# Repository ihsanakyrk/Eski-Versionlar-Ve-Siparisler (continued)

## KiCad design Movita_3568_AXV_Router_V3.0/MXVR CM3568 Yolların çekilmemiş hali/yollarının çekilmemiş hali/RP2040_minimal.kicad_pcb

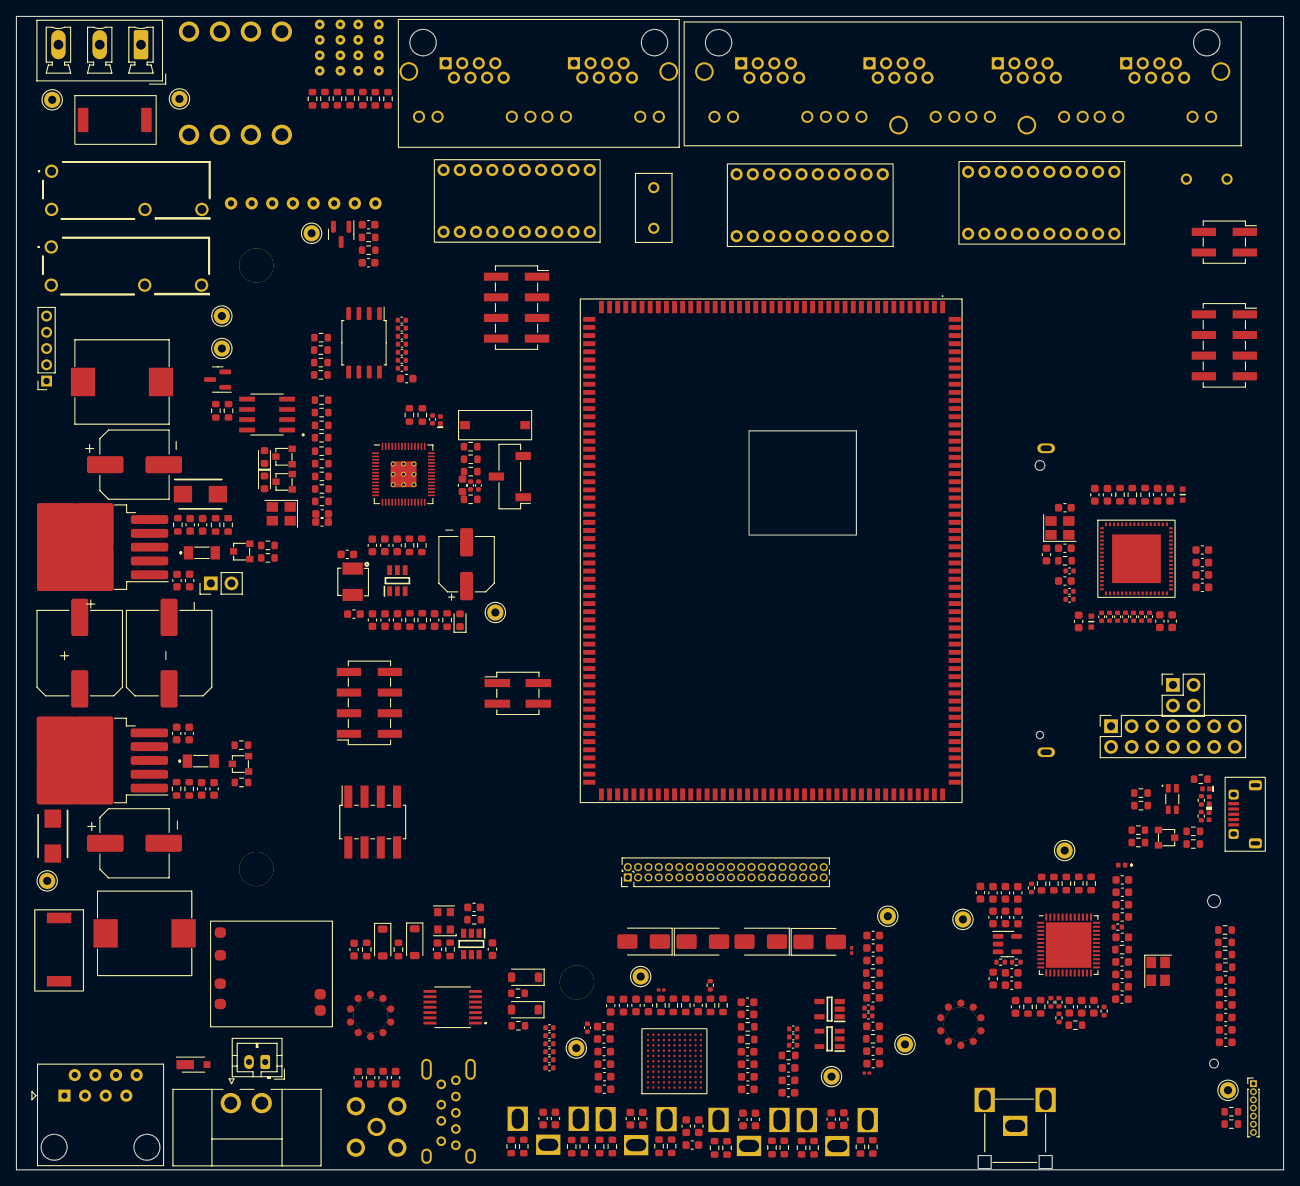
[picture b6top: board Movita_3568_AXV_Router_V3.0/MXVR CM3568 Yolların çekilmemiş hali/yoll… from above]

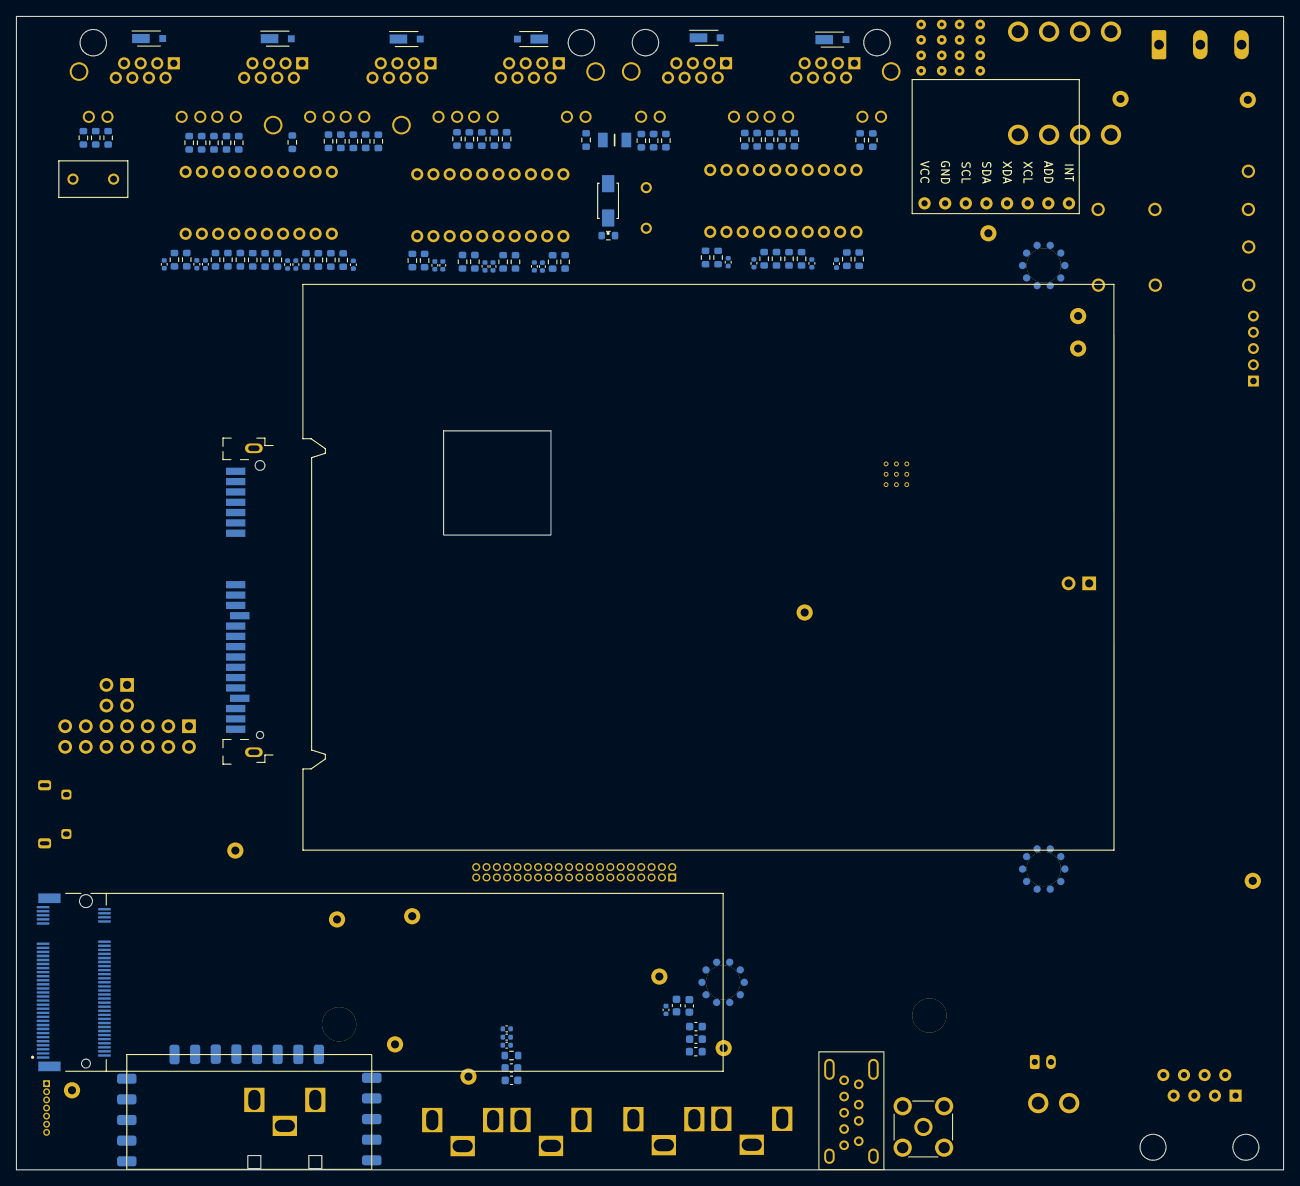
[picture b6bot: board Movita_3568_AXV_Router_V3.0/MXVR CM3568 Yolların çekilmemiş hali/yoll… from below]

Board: 4 copper layers, 156.0 x 142.0 mm, 480 parts (108 on the bottom side), 341 nets, no tracks yet.

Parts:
C1, C2, C3, C31, C40, C41, C42, C43, C44, C45, C46, C47, C48, C49, C50, C51, C52, C54, C55, C56, C57, C58, C59, C60, C101, C102, C103, C104, C105, C106, C107, C108, C109, C110, C116, C117, C118, C119, C120, C121, C124, C125, C126, C127, C143, C144, C147, C148, C150, C152, C156, C157, C158, C159, C160, C161, C162, C163, C165, C182, C183: 0.1uF; C_0603_1608Metric
C4, C6, C12: 4.7uF; C_0201_0603Metric
C7, C10, C37, C151, C155: 10uF; C_0603_1608Metric
C8, C9, C11, C13, C16, C17, C20, C21, C22, C23, C24, C25, C26, C27: 100nF; C_0402_1005Metric
C14, C15: 27pF; C_0603_1608Metric
C18, C19, C53, C128, C139, C140: 1uF; C_0603_1608Metric
C28, C83: 220uF/50V; C_Elec_10x10.2
C29, C30, C84, C169, C170, C172: 1uF/50V; C_0603_1608Metric
C32, C82: 330uF/25V; C_Elec_8x10.2
C35, C94, C166: 10pF; C_0603_1608Metric
C36, C38, C74, C75, C77, C95, C96, C97, C98, C99, C100, C111, C178: 100nF; C_0603_1608Metric
C39, C61: 33pF; C_0603_1608Metric
C62, C69, C180, C181: 22uF; C_0603_1608Metric
C63, C64, C65, C66, C67, C68, C70, C71, C72, C73, C76, C78, C79, C80, C81, C85, C86, C87, C88, C89, C90, C91: 0.1uF; C_0402_1005Metric
C92, C93: 1000PF 2KV; S102K33Y5PP63K5R
C112, C113, C129, C130, C131, C132, C133, C134, C135, C136, C137, C138, C141, C142: 10uF; C_0402_1005Metric
C114, C115: 4.7uF; C_0402_1005Metric
C122, C123: 8pF; C_0603_1608Metric
C145, C146, C179: 22pF; C_0603_1608Metric
C149, C154: 4.7uF; C_0603_1608Metric
C153: 10nF; C_0603_1608Metric
C164: DNP; C_0603_1608Metric
C171, C174: 0.33uF 16V; C_0603_1608Metric
C175, C176, C177: 10uF /16V; C_0603_1608Metric
C184: 220uF/16V; CP_Elec_6.3x7.7
D1, D2, D4, D5, D7, D8, D9: 2SS100L-W; 2SS100LW
D3: SS14; DIOM4325X250N
D6, D12, D13, D30: ESD5341N
D10, D11: SS54B; DIOM5336X244N
D14, D15, D16, D17: B5819W; D_SOD-123
D18, D19, D20, D21: SMAJ30CA; D_SMA
D22: ESD5451N
D23, D24: LL4148
D25: LED; LED_0603_1608Metric
D26, D27: MRA4007T3G; D_0603_1608Metric
D28, D29: S6MC
FB1: HI1206N101R-10; BEADC3216X130N
FL1: DLW31SN900SQ2L; DLW31SH222SQ2L
FL3, FL4: BLM18PG121SN1D; BLM18AG102BH1D
IC1: SN74LVC125APWR
IC2: MS1836S_QFN48-7x7; QFN-48-1EP_7x7mm_P0.5mm_EP5.6x5.6mm
IC3: RTL8309N
IC5: SY8113B; SOT95P285X100-6N
J1: FEMALE SMD Pin Header; PinSocket_2x07_P2.54mm_Vertical
J2, J18, J19, J20, J26: Phono RCA Jack Mono Connector Solder (Boktech adv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; AV_CON
J3: DNP; PinSocket_2x04_P2.54mm_Vertical_SMD
J4: DNP; PinSocket_1x05_P2.00mm_Vertical
J5: RJ45; RJ45_Amphenol_54602-x08_Horizontal
J6: MALE SMD Pin Header; PinHeader_2x20_P1.27mm_Vertical
J7: Conn_01x02_Socket; KF2EDGH-3.81-2P
J8: APCI0079-P002A J8900 M.2 M Key; TE_1-2199119-5
J9: Conn_01x06_Pin; RTL8188EU
J10: SMA Connetor_inner_hole; SMA_Connector_inner_pin_right_angle
J11: Conn_01x03_Socket; KF2EDGR-Y-5.08-3P-Right Angle
J12: Conn_01x08_Socket; KF2EDGH-3.81_8P
J13: FEMALE SMD Pin Header; PinSocket_2x04_P2.00mm_Vertical_SMD
J14: KH-MICRO5P-JN
J15, J16: Conn_01x08_Socket; LED_4_Block
J17: Conn_01x02_Socket; JST_PH_B2B-PH-K_1x02_P2.00mm_Vertical
J21, J22: FEMALE SMD Pin Header; PinSocket_2x04_P2.54mm_Vertical_SMD
J23, J28: M3x*0.5 L=10; Screw_terminal_shinbo
J24: USB 3.0 AF; CP-USB-3015
J25: DNP; PinHeader_2x02_P2.54mm_Vertical_SMD
J27: DNP; PinHeader_1x07_P1.00mm_Vertical
J29, J30: M3x*0.5 L=6; Screw_terminal_shinbo
J31: Conn_01x04_Socket; PinSocket_2x02_P2.54mm_Vertical
J32: DNP; PinHeader_1x02_P2.54mm_Vertical
J33: Conn_01x04_Socket; PinSocket_2x02_P2.54mm_Vertical_SMD
J34: FEMALE SMD Pin Header; PinSocket_1x03_P2.54mm_Vertical_SMD_Pin1Left
J35: M3x*0.5 L=3; Screw_terminal_shinbo
K1, K3: HF46F_5-HS1; HF46F5HS1
L2, L3: 47uH 5A; L_Bourns_SRR1208_12.7x12.7mm
L4, L5: FB/100R; L_0603_1608Metric
L6: UPZ1608E101-3R0TF; L_0603_1608Metric
L7: MLI1608F-1R2KT; L_0603_1608Metric
L8: HA42-4R7MT; Inductor_0402_4.7uH
L9: 2.7nH; L_0603_1608Metric
PS2: RT9013-33GB; SOT94P279X130-5N
PS3: TLV75712PDBVR; SOT95P280X145-5N
Q1: 2N3904S-RTK/PS; 2N3904S-RTKPS
Q2, Q3, Q4, Q5: MMBT2222ALT1G
R1: 150R; R_0603_1608Metric
R2, R3, R18, R19, R20, R35, R36, R40, R41, R43, R44, R47, R49, R55, R58, R59, R60, R61, R62, R63, R64, R65, R66, R67, R68, R69, R70, R71, R72, R78, R80, R82, R94, R95, R96, R97, R98, R99, R100, R101, R104, R107, R119, R122, R124, R136, R137, R155, R158, R159, R164, R169, R171: 10K; R_0603_1608Metric
R4, R5, R7, R9, R11, R25, R46, R54, R109, R113, R123, R126, R127: 0R; R_0603_1608Metric
R6, R8: 2.49K 1%; R_0603_1608Metric
R10, R12, R13, R21, R23, R24, R37, R38, R39, R42, R48, R77, R79, R81, R83, R84, R85, R86, R87, R88, R89, R90, R91, R92, R93, R105, R106, R132, R170, R172: 1K; R_0603_1608Metric
R14: 200R; R_0603_1608Metric
R15: 1R; R_0603_1608Metric
R16, R17: 27R; R_0603_1608Metric
R22, R26, R29, R50, R154, R163, R167, R173: DNP; R_0603_1608Metric
R27, R28, R32, R33, R34, R117, R118, R120: 4.7K; R_0603_1608Metric
R30, R31: 2.2R; R_0402_1005Metric
R45, R53, R108, R112, R116, R125, R146: 100R; R_0603_1608Metric
R51, R52, R56, R57, R73, R74, R75, R76, R102, R103, R110, R111, R114, R115: 75R; R_0603_1608Metric
R121, R129, R138: DNP; R_0402_1005Metric
R128: 560K; R_0603_1608Metric
R130: 10K %1; R_0402_1005Metric
R131, R133, R134, R139: 0R; R_0402_1005Metric
R135: 330R %1; R_0603_1608Metric
R140, R141: 2.2K; R_0603_1608Metric
R142: 22R; R_0603_1608Metric
R143: 75R; R_0402_1005Metric
R144: 100K; R_0603_1608Metric
R145: 1K %5; R_0603_1608Metric
R147, R148, R149, R150, R151, R152, R153: 220R; R_0603_1608Metric
R156: 3.3K 1%; R_0603_1608Metric
R157, R160: 470R; R_0603_1608Metric
R161: 15K; R_0603_1608Metric
R162: 1.6K; R_0603_1608Metric
R165: 232K_1%; R_0603_1608Metric
R166: 51K_1%; R_0603_1608Metric
R168: 2K; R_0603_1608Metric
S1: TS-1101-C-W
TP1, TP2, TP3, TP4, TP5, TP6, TP7, TP8, TP9, TP10, TP11, TP12, TP13, TP14, TP15: TestPoint; Pin_D1.0mm_L10.0mm
U1: CM3568
U2, U3: TLV76033DBZT; SOT-23
U4: 3N27000G33YC; Oscillator_SMD_EuroQuartz_XO32-4Pin_3.2x2.5mm
U5: RP2040; RP2040-QFN-56
U6: MAX485E; SOIC127P600X175-8N
U6B1: Nextchip N4; N4
U7: W25Q128JVS; SOIC-8_5.23x5.23mm_P1.27mm
U8: NL27WZU04DTT1G; SOP95P275X110-6N
U9: DNP; HDMI
U10, U15: XL4015; TO-263-5_TabPin3
U11: DNP; module_mpu6050
U12, U13, U19: UTH20T29 2220X; RJ45_Transformer_2_Port
U14: RT9013-12GB; SOT-23-5
U16: 5622-1200-ML; SATA_Connector_5622-1200-ML
U17: RJ45-4-Block; 4_Block_RJ45
U18: 2_Block_RJ45
Y1: 12000Mhz; Crystal_SMD_3225-4Pin_3.2x2.5mm
Y2: X322527MSB4SI; Crystal_SMD_3225-4Pin_3.2x2.5mm
Y4: 25MHz; Crystal_SMD_3225-4Pin_3.2x2.5mm

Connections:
1V0: C38.2, C74.2, C75.2, C95.2, C97.2, FL4.2, IC3.33 (DVDDL_2)
1V0PLL: C99.2, C100.2, FL4.1
3.3V_Sensor: C36.1, C41.1, D3.A, R27.1, R28.2, U2.1 (OUT), U11.1 (VCC)
3V3: C96.2, C98.2
+1V1: C16.1, C17.1, C18.1, U5.23 (DVDD), U5.45 (VREG_VOUT), U5.50 (DVDD)
/4 Port RJ45 and Transformer/+3.3V: C2.1, C4.1, C7.1, C55.1, C56.1, C57.1, C58.1, C59.1, C60.1, C114.1, C118.1, C179.2, C180.2, C181.2, C182.2, C183.2, C184.1, FB1.1, FL3.1, J6.5, J6.6, J8.2, J8.4, J8.12, J8.14, J8.16, J8.18, J8.70, J8.72, J8.74, J9.1, J21.1, L6.1, L8.2, PS3.1 (IN), R3.2, R154.1, R165.1, R168.1, TP3.1, TP9.1
/4 Port RJ45 and Transformer/LED0: IC3.38 (P0LED/DIS_EEE), R37.1, R38.2, R72.2
/4 Port RJ45 and Transformer/LED1: IC3.39 (P1LED/LED_MODE[1]), R23.1, R24.2, R78.2
/4 Port RJ45 and Transformer/LED2: IC3.40 (P2LED/LED_MODE[2]), R39.1, R42.2, R80.2
/4 Port RJ45 and Transformer/LED3: IC3.42 (P3LED/RMAMODE), R82.2, R84.1, R85.2
/4 Port RJ45 and Transformer/LED4: IC3.43 (P4LED/UNKOWN_MULTI), R86.1, R87.2, R104.2
/4 Port RJ45 and Transformer/LED5: IC3.44 (P5LED/DIS_RST_BLNK), R88.1, R89.2, R107.2
/4 Port RJ45 and Transformer/RXI_0_N: IC3.57 (RXIN0), R71.2, U13.9
/4 Port RJ45 and Transformer/RXI_0_P: IC3.56 (RXIP0), R70.2, U13.10
/4 Port RJ45 and Transformer/RXI_1_N: IC3.63 (RXIN1), R64.2, U13.2
/4 Port RJ45 and Transformer/RXI_1_P: IC3.64 (RXIP1), R65.2, U13.1
/4 Port RJ45 and Transformer/RXI_2_N: IC3.3 (RXIN2), R63.2, U12.9
/4 Port RJ45 and Transformer/RXI_2_P: IC3.2 (RXIP2), R62.2, U12.10
/4 Port RJ45 and Transformer/RXI_3_N: IC3.9 (RXIN3), R47.2, U12.2
/4 Port RJ45 and Transformer/RXI_3_P: IC3.10 (RXIP3), R55.2, U12.1
/4 Port RJ45 and Transformer/RXI_4_N: IC3.14 (RXIN4), R95.2, U19.9
/4 Port RJ45 and Transformer/RXI_4_P: IC3.13 (RXIP4), R94.2, U19.10
/4 Port RJ45 and Transformer/RXI_5_N: IC3.20 (RXIN5), R99.2, U19.2
/4 Port RJ45 and Transformer/RXI_5_P: IC3.21 (RXIP5), R98.2, U19.1
/4 Port RJ45 and Transformer/TXO_0_N: IC3.58 (TXON0), R69.2, U13.7
/4 Port RJ45 and Transformer/TXO_0_P: IC3.59 (TXOP0), R68.2, U13.6
/4 Port RJ45 and Transformer/TXO_1_N: IC3.62 (TXON1), R66.2, U13.4
/4 Port RJ45 and Transformer/TXO_1_P: IC3.61 (TXOP1), R67.2, U13.5
/4 Port RJ45 and Transformer/TXO_2_N: IC3.4 (TXON2), R61.2, U12.7
/4 Port RJ45 and Transformer/TXO_2_P: IC3.5 (TXOP2), R60.2, U12.6
/4 Port RJ45 and Transformer/TXO_3_N: IC3.8 (TXON3), R58.2, U12.4
/4 Port RJ45 and Transformer/TXO_3_P: IC3.7 (TXOP3), R59.2, U12.5
/4 Port RJ45 and Transformer/TXO_4_N: IC3.15 (TXON4), R96.2, U19.7
/4 Port RJ45 and Transformer/TXO_4_P: IC3.16 (TXOP4), R97.2, U19.6
/4 Port RJ45 and Transformer/TXO_5_N: IC3.19 (TXON5), R100.2, U19.4
/4 Port RJ45 and Transformer/TXO_5_P: IC3.18 (TXOP5), R101.2, U19.5
/+12V: C32.1, C172.2, C174.2, C175.2, C176.2, C177.2, D1.2, D2.2, D4.2, D5.2, D7.2, D8.2, D9.2, IC5.5 (IN), J12.4, L3.2, R11.2, R161.1, R163.1, TP2.1, U16.P13 (VCC12), U16.P14 (VCC12), U16.P15 (VCC12), U17.P1_L_Led+, U17.P2_L_Led+, U17.P3_L_Led+, U17.P4_L_Led+, U18.P1_L_Led+, U18.P2_L_Led+
/CM3568/+5V: C1.1, C3.1, C6.1, C10.1, C82.1, C84.2, C115.1, C119.1, C171.2, D26.1 (K), D27.1 (K), J16.5, J21.2, J21.4, J24.1 (VBUS), K1.2 (COIL_2), K3.2 (COIL_2), L2.2, PS2.1 (VIN), R25.2, R32.1, R155.1, TP1.1, TP8.1, U1.143, U1.144, U16.P7 (VCC5), U16.P8 (VCC5), U16.P9 (VCC5)
/CM3568/GPIO4_C5_d: J34.1, R167.2, U1.156
/CM3568/GPIO4_C6_d: J34.2, U1.157, U5.26 (RUN)
/CM3568/HDMITX_CEC_M0: R142.1, U1.162, U9.17
/CM3568/HDMITX_SCL: IC2.46 (RXDDC_SCL), R141.1, U1.164, U9.20
/CM3568/HDMITX_SDA: IC2.45 (RXDDC_SDA), R140.1, U1.163, U9.19
/CM3568/HDMI_TX0N: IC2.4 (HDMI_RX0N), U1.1, U9.8
/CM3568/HDMI_TX0P: IC2.5 (HDMI_RX0P), U1.2, U9.7
/CM3568/HDMI_TX1N: IC2.7 (HDMI_RX1N), U1.3, U9.6
/CM3568/HDMI_TX1P: IC2.8 (HDMI_RX1P), U1.4, U9.5
/CM3568/HDMI_TX2N: IC2.10 (HDMI_RX2N), U1.5, U9.3
/CM3568/HDMI_TX2P: IC2.11 (HDMI_RX2P), U1.6, U9.2
/CM3568/HDMI_TXCLKN_PORT: IC2.1 (HDMI_RXCN), U1.201, U9.11
/CM3568/HDMI_TXCLKP_PORT: IC2.2 (HDMI_RXCP), U1.202, U9.10
/CM3568/HDMI_TX_HPDIN: R144.1, R145.2, U1.7, U9.16
/CM3568/MIC1_INN: J27.5, U1.122
/CM3568/PCIE20_REFCLKN: J3.6, J8.53, U1.9
/CM3568/PCIE20_REFCLKP: J3.5, J8.55, U1.8
/CM3568/PCIE20_RXN: J3.3, J8.43, U1.11
/CM3568/PCIE20_RXP: J3.4, J8.41, U1.10
/CM3568/PCIE20_TXN: J3.2, J8.47, U1.13
/CM3568/PCIE20_TXP: J3.1, J8.49, U1.12
/CM3568/PDM_SDI2_M0_ADC/PCIE20_WAKEn_M2: J8.54, U1.91
/CM3568/PHY1_MDI0+: IC3.28 (TXOP7), J33.1, U1.102
/CM3568/PHY1_MDI0-: IC3.29 (TXON7), J33.2, U1.103
/CM3568/PHY1_MDI1+: IC3.31 (RXIP7), J33.3, U1.104
/CM3568/PHY1_MDI1-: IC3.30 (RXIN7), J33.4, U1.105
/CM3568/RESETn: J27.1, U1.145
/CM3568/RK809_PWRON: J27.6, R26.1, R29.1, TP15.1, U1.141
/CM3568/SARADC_VIN0_KEY/RECOVERY: R146.1, U1.65
/CM3568/SATA0_RXN: U1.20, U16.S5 (RX-)
/CM3568/SATA0_RXP: U1.21, U16.S6 (RX+)
/CM3568/SATA0_TXN: U1.18, U16.S3 (TX-)
/CM3568/SATA0_TXP: U1.19, U16.S2 (TX+)
/CM3568/UART0_RX/PWM1_M0: U1.72, U5.27 (GPIO16)
/CM3568/UART0_TX/GPIO0_C1: U1.71, U5.28 (GPIO17)
/CM3568/USB2_HOST2_DM: J13.7, J22.4, U1.96
/CM3568/USB2_HOST2_DP: J13.5, J22.3, U1.97
/CM3568/USB2_HOST3_DM: J9.2, J22.6, U1.98
/CM3568/USB2_HOST3_DP: J9.3, J22.5, U1.99
/CM3568/USB3_HOST1_DM: J22.2, J24.2 (D-), U1.23
/CM3568/USB3_HOST1_DP: J22.1, J24.3 (D+), U1.24
/CM3568/USB3_HOST1_SSRXN: J24.5 (SSRX-), U1.16
/CM3568/USB3_HOST1_SSRXP: J24.6 (SSRX+), U1.17
/CM3568/USB3_HOST1_SSTXN: J24.8 (SSTX-), U1.14
/CM3568/USB3_HOST1_SSTXP: J24.9 (SSTX+), U1.15
/CM3568/USB3_OTG0_DM: FL1.4, R30.1, U1.26
/CM3568/USB3_OTG0_DP: FL1.1, R31.1, U1.25
/CM3568/USB3_OTG0_ID: D13.1, J14.4 (ID), R34.2, U1.55
/CM3568/USB3_OTG0_VBUSDET: R32.2, R33.1, U1.54
/CM3568/VCC_1V8_OUTPUT: C12.1, C31.1, R119.1, R122.1, TP10.1, U1.146
/CM3568/VRTC: J27.7, R1.2, U1.124
/CSI_AHD/AHD_RESET: C109.1, R122.2, R123.1, U6B1.K10 (RESETN)
/CSI_AHD/AVIN: D18.2 (A2), D19.2 (A2), D20.2 (A2), D21.2 (A2), J18.1, J18.2, J19.1, J19.2, J20.1, J20.2, J26.1, J26.2, R46.1, R54.1, R109.1, R113.1
/CSI_AHD/COAX1: IC1.2 (1A), U6B1.C2 (MPP1)
/CSI_AHD/COAX2: IC1.5 (2A), U6B1.C3 (MPP2)
/CSI_AHD/COAX3: IC1.9 (3A), U6B1.C4 (MPP3)
/CSI_AHD/COAX4: IC1.12 (4A), U6B1.C5 (MPP4)
/CSI_AHD/GPIO2_C6: R119.2, U6B1.H8 (IRQ)
/CSI_AHD/GPIO4_C4_d: IC1.10 (3~OE), R43.1
/CSI_AHD/LCDC_D22/UART3_TX_M1: IC1.13 (4~OE), R44.1
/CSI_AHD/LCDC_D23/UART3_RX_M1: IC1.1 (1~OE), R35.1
/CSI_AHD/PDM_CLK1_M0_ADC/SPDIF_TX_M0: IC1.4 (2~OE), R36.1
/CSI_AHD/SYS_CLK: R45.1, U8.6 (OUT*Y1)
/CSI_AHD/VINN1: C102.2, U6B1.E2 (VINN1)
/CSI_AHD/VINN2: C104.2, U6B1.G2 (VINN2)
/CSI_AHD/VINN3: C106.2, U6B1.J2 (VINN3)
/CSI_AHD/VINN4: C108.2, U6B1.L2 (VINN4)
/CSI_AHD/VINP1: C101.2, U6B1.D1 (VINP1)
/CSI_AHD/VINP2: C103.2, U6B1.F1 (VINP2)
/CSI_AHD/VINP3: C105.2, U6B1.H1 (VINP3)
/CSI_AHD/VINP4: C107.2, U6B1.K1 (VINP4)
/CSI_AHD/VIN_N1: C102.1, R52.2
/CSI_AHD/VIN_N2: C104.1, R57.2
/CSI_AHD/VIN_N3: C106.1, R111.2
/CSI_AHD/VIN_N4: C108.1, R115.2
/CSI_AHD/VIN_P1: C101.1, D15.1 (K), R46.2, R51.2
/CSI_AHD/VIN_P2: C103.1, D14.1 (K), R54.2, R56.2
/CSI_AHD/VIN_P3: C105.1, D17.1 (K), R109.2, R110.2
/CSI_AHD/VIN_P4: C107.1, D16.1 (K), R113.2, R114.2
/EC25_Sim/GSM_STATUS: J13.3, J16.6
/HDMI_CVBS/CVideo_OUT: C164.2, C165.1, D22.1, J2.1, J2.2, J31.1, L7.2
/HDMI_CVBS/DAC_R: C163.1, C164.1, IC2.31 (AV_OUT), L7.1, R143.2
/HDMI_CVBS/HDMI_RX_HPD: IC2.43 (HDMIRX_HPD), R145.1
/HDMI_CVBS/P/N_SEL: R131.1, R137.2, R138.1
/HDMI_CVBS/RSTn: C153.1, IC2.15 (RSTn), R136.1, R142.2
/HDMI_CVBS/RX_DET: IC2.42 (DVDD33_1), IC2.44 (HDMIRX_DET), R132.2
/HDMI_CVBS/VDD10_EPHY: C155.1, C157.1, C158.1, C159.1, C160.1, C161.1, C162.1, IC2.3 (AVDD12), IC2.9 (AVDD12_1), IC2.20 (DVDD12), IC2.40 (DVDD12_1), TP11.1, U14.5 (OUT)
/HDMI_CVBS/XTAL1: C145.1, IC2.27 (XTOUT), Y2.1
/HDMI_CVBS/XTAL2: C146.1, IC2.26 (XTIN), Y2.3
/IO Connector/FLASH: J12.5, K3.4 (COM)
/IO Connector/HORN: J12.6, K1.4 (COM)
/MIC+: J12.1, J27.4, U1.123
/Power Unit/+3V3_Mini: C19.1, C20.1, C21.1, C22.1, C23.1, C24.1, C25.1, C26.1, C27.1, R14.1, R18.2, R19.2, R22.1, R40.2, R41.2, R157.1, R160.1, U3.1 (OUT), U5.1 (IOVDD), U5.10 (IOVDD), U5.22 (IOVDD), U5.33 (IOVDD), U5.42 (IOVDD), U5.44 (VREG_IN), U5.48 (USB_VDD), U5.49 (IOVDD), U6.8 (VCC), U7.8 (VCC)
/RP2040/GPIO0: R27.2, U5.2 (GPIO0), U11.4 (SDA)
/RP2040/GPIO1: R28.1, U5.3 (GPIO1), U11.3 (SCL)
/RP2040/GPIO6: R147.1, U5.8 (GPIO6)
/RP2040/GPIO7: R171.1, R172.1, U5.9 (GPIO7)
/RP2040/GPIO8: R169.1, R170.1, U5.11 (GPIO8)
/RP2040/GPIO9: R148.1, U5.12 (GPIO9)
/RP2040/GPIO10: R149.1, U5.13 (GPIO10)
/RP2040/GPIO11: R150.1, U5.14 (GPIO11)
/RP2040/GPIO12: R151.1, U5.15 (GPIO12)
/RP2040/GPIO13: R152.1, U5.16 (GPIO13)
/RP2040/GPIO14: R153.1, U5.17 (GPIO14)
/RP2040/GPIO15: R20.2, R50.1, U5.18 (GPIO15)
/RP2040/GPIO19: R167.1, U5.30 (GPIO19)
/RP2040/GPIO20: R164.2, U5.31 (GPIO20)
/RP2040/GPIO21: J13.6, U5.32 (GPIO21)
/RP2040/GPIO22: R158.1, U5.34 (GPIO22)
/RP2040/GPIO23: R159.1, R173.1, U5.35 (GPIO23)
/RP2040/GPIO27_ADC1: D30.1, R48.1, R49.2, U5.39 (GPIO27_ADC1)
/RP2040/QSPI_SCLK: U5.52 (QSPI_SCLK), U7.6 (CLK)
/RP2040/QSPI_SD0: U5.53 (QSPI_SD0), U7.5 (DI(IO0))
/RP2040/QSPI_SD1: U5.55 (QSPI_SD1), U7.2 (DO(IO1))
/RP2040/QSPI_SD2: U5.54 (QSPI_SD2), U7.3 (IO2)
/RP2040/QSPI_SD3: U5.51 (QSPI_SD3), U7.7 (IO3)
/RP2040/QSPI_SS: R21.1, R22.2, U5.56 (QSPI_SS), U7.1 (~CS)
/RP2040/XIN: C14.1, U5.20 (XIN), Y1.3
/RP2040/XOUT: R13.1, U5.21 (XOUT)
/RP2040/~USB_BOOT: J4.3, R21.2
/RTL8309E/LED6: IC3.45 (P6LED), R90.1, R91.2
/RTL8309E/LED7: IC3.46 (P7LED), R92.1, R93.2
/SPK+: J12.3, J27.3, U1.118
/SPK-: J12.2, J27.2, U1.119
ADC_VREF: R14.2, R15.1
AVDD12: C129.1, C131.1, C133.1, C135.1, C137.1, C141.1, L4.1, PS3.5 (OUT), R126.1, R127.1, TP14.1, U6B1.D3 (AVDD12_CH1), U6B1.F3 (AVDD12_CH2), U6B1.H3 (AVDD12_CH3), U6B1.K3 (AVDD12_CH4)
AVDD12PLL: C140.1, C144.1, R127.2, U6B1.H4 (AVDD12_PLL)
AVDD12_MIPI: C139.1, C143.1, R126.2, U6B1.J7 (AVDD12_MIPI)
AVDD33: C53.1, C110.1, C130.1, C132.1, C134.1, C136.1, C138.1, C142.1, IC1.14 (VCC), L5.2, PS2.5 (VOUT), TP13.1, U6B1.E3 (AVDD33.1), U6B1.G3 (AVDD33.2), U6B1.J3 (AVDD33.3), U6B1.L3 (AVDD33.4)
CMT1: R76.2, U13.13
CMT2: R75.2, U13.18
CMT3: R74.2, U12.13
CMT4: R73.2, U12.18
CMT5: R103.2, U19.13
CMT6: R102.2, U19.18
CT: C8.1, C9.1, C11.1, C13.1, C62.1, C63.1, C64.1, C65.1, C66.1, C67.1, C68.1, C69.1, C71.1, C72.1, C73.1, C76.2, FL3.2, IC3.41 (DVDDH), IC3.49 (V33IN), IC3.50 (AVDDHPLL), IC3.60 (AVDDH_4), R8.1, R10.2, R23.2, R37.2, R39.2, R84.2, R86.2, R88.2, R90.2, R92.2, U12.3, U12.8, U13.3, U13.8, U19.3, U19.8
DVDD33: R120.1, U6B1.D5 (DVDD33.1), U6B1.D7 (DVDD33.3), U6B1.E8 (DVDD33.5), U6B1.G7 (DVDD33.4), U6B1.H6 (DVDD33.2)
Earth: C1.2, C2.2, C3.2, C4.2, C6.2, C7.2, C8.2, C9.2, C10.2, C11.2, C12.2, C13.2, C14.2, C15.2, C16.2, C17.2, C18.2, C19.2, C20.2, C21.2, C22.2, C23.2, C24.2, C25.2, C26.2, C27.2, C28.2, C29.1, C31.2, C32.2, C36.2, C37.2, C39.2, C40.1, C41.2, C42.1, C43.1, C44.1, C45.1, C46.1, C47.1, C48.1, C53.2, C54.2, C55.2, C56.2, C57.2, C58.2, C59.2, C60.2, C61.2, C62.2, C63.2, C64.2, C65.2, C66.2, C67.2, C68.2, C69.2, C70.2, C71.2, C72.2, C73.2, C77.2, C78.2, C79.2, C80.2, C81.2, C82.2, C83.2, C84.1, C85.2, C86.2, C87.2, C88.2, C89.2, C90.2, C91.2, C92.1, C94.2, C109.2, C110.2, C111.2, C112.2, C113.2, C114.2, C115.2, C116.2, C117.2, C118.2, C119.2, C120.2, C121.2, C122.1, C123.1, C124.2, C125.2, C126.2, C127.2, C128.2, C129.2, C130.2, C131.2, C132.2, C133.2, C134.2, C135.2, C136.2, C137.2, C138.2, C139.2, C140.2, C141.2, C142.2, C143.2, C144.2, C145.2, C146.2, C147.2, C148.2, C149.2, C150.2, C151.2, C152.2, C153.2, C154.2, C155.2, C156.2, C157.2, C158.2, C159.2, C160.2, C161.2, C162.2, C163.2, C165.2, C166.2, C169.1, C172.1, C175.1, C176.1, C177.1, C180.1, C181.1, C182.1, C183.1, C184.2, D6.2, D10.2, D11.2, D12.2, D13.2, D18.1 (A1), D19.1 (A1), D20.1 (A1), D21.1 (A1), D22.2, D25.1 (K), D30.2, IC1.7 (GND), IC2.19 (VSS), IC2.22 (VREF_L), IC2.30 (VSS_1), IC2.41 (VSS_2), IC2.49 (GND(EPAD)), IC3.65 (EP), IC5.2 (GND), J2.3, J4.4, J5.7, J5.8, J6.3, J6.4, J6.7, J6.8, J6.15, J6.16, J6.19, J6.20, J6.31, J6.32, J7.1, J8.1, J8.3, J8.9, J8.15, J8.21, J8.27, J8.33, J8.39, J8.45, J8.51, J8.57, J8.71, J8.73, J8.75, J8.SH1 (SHIELD), J8.SH2 (SHIELD), J9.4, J9.5, J10.2, J10.3, J10.4, J10.5, J11.2, J13.1, J13.2, J14.5 (GND), J14.SHIELD, J15.1, J15.3, J15.5, J15.7, J16.1, J16.3, J16.7, J17.1, J21.5, J21.6, J24.4 (GND), J24.7 (DRAIN), J24.10 (SHIELD), J31.2, J32.2, J34.3, PS2.2 (GND), PS3.2 (GND), Q1.2 (E), Q2.2 (E), Q3.2 (E), Q4.2 (E), Q5.2 (E), R6.2, R12.1, R24.1, R26.2, R33.2, R35.2, R36.2, R38.1, R42.1, R43.2, R44.2, R48.2, R50.2, R53.2, R77.2, R79.2, R81.2, R83.2, R85.1, R87.1, R89.1, R91.1, R93.1, R105.2, R106.2, R108.2, R112.1, R116.2, R117.2, R118.2, R121.2, R129.1, R130.1, R133.1, R135.1, R138.2, R143.1, R144.2, R156.2, R162.2, R166.2, R169.2, R171.2, S1.2, U1.22, U1.38, U1.62, U1.66, U1.95, U1.110, U1.140, U1.161, U1.190, U2.3 (GND), U3.3 (GND), U4.2 (GND2), U4.4 (GND1), U5.19 (TESTEN), U5.57 (GND), U6.5 (GND), U6B1.A1 (N.C1), U6B1.A11 (N.C2), U6B1.E5 (VSS3), U6B1.E6 (VSS6), U6B1.E7 (VSS8), U6B1.F4 (VSS1), U6B1.F5 (VSS4), U6B1.F6 (VSS7), U6B1.F7 (VSS9), U6B1.G4 (VSS2), U6B1.G5 (VSS5), U6B1.J4 (TEST1), U6B1.J8 (AVSS_MIPI), U6B1.K4 (TEST0), U6B1.K11 (TEST_CLK1), U6B1.L1 (N.C3), U6B1.L10 (TEST_CLK2), U6B1.L11 (N.C4), U7.4 (GND), U8.2 (GND), U9.4, U9.9, U9.12, U9.18, U10.1 (GND), U11.2 (GND), U14.2 (GND), U15.1 (GND), U16.GND, U16.P4 (GND), U16.P5 (GND), U16.P6 (GND), U16.P10 (GND), U16.P11 (GND), U16.P12 (GND), U16.S1 (GND), U16.S4 (GND), U16.S7 (GND), U17.7_1, U17.7_2, U17.7_3, U17.7_4, U17.8_1, U17.8_2, U17.8_3, U17.8_4, U18.7_1, U18.7_2, U18.8_1, U18.8_2, U18.SHIELD, Y1.2, Y1.4, Y2.2, Y2.4, Y4.2, Y4.4
GNDPWR: C92.2, C93.2, U17.SHIELD
LED_VDD: FB1.2, U17.P1_R_Led+, U17.P2_R_Led+, U17.P3_R_Led+, U17.P4_R_Led+, U18.P1_R_Led+, U18.P2_R_Led+
LIND_DS_LED: IC3.37 (LDIND/DIS_LD), R10.1, R12.2
unnamed: C15.1, R13.2, Y1.1
unnamed: C35.1, C94.1, L9.1
unnamed: C70.1, R47.1, R55.1
unnamed: C78.1, R94.1, R95.1
unnamed: C79.1, R96.1, R97.1
unnamed: C80.1, R98.1, R99.1
unnamed: C81.1, R100.1, R101.1
unnamed: C85.1, R58.1, R59.1
unnamed: C86.1, R60.1, R61.1
unnamed: C87.1, R62.1, R63.1
unnamed: C88.1, R64.1, R65.1
unnamed: C89.1, R66.1, R67.1
unnamed: C90.1, R68.1, R69.1
unnamed: C91.1, R70.1, R71.1
unnamed: C93.1, R73.1, R74.1, R75.1, R76.1, R102.1, R103.1
unnamed: C113.1, C117.1, C121.1, C125.1, C127.1, L5.1
unnamed: D3.C, R1.1
unnamed: D14.2 (A), IC1.6 (2Y)
unnamed: D15.2 (A), IC1.3 (1Y)
unnamed: D16.2 (A), IC1.11 (4Y)
unnamed: D17.2 (A), IC1.8 (3Y)
unnamed: D25.2 (A), R168.2
unnamed: D26.2 (A), K1.1 (COIL_1), Q4.3 (C)
unnamed: D27.2 (A), K3.1 (COIL_1), Q5.3 (C)
unnamed: IC2.29 (DAC_REF), R135.2
unnamed: IC2.16 (KEY0), R131.2
unnamed: IC2.17 (KEY1), R133.2
unnamed: IC2.12 (MCU_SEL), R129.2
unnamed: IC2.48 (REXT), R130.2
unnamed: C151.1, C152.1, IC2.25 (VMID)
unnamed: C149.1, C150.1, IC2.23 (VREF_H), R134.1
unnamed: C76.1, IC3.6 (AVDDH_1)
unnamed: C98.1, IC3.17 (AVDDH_2)
unnamed: C96.1, IC3.27 (AVDDH_3)
unnamed: C99.1, IC3.53 (AVDDLPLL)
unnamed: C74.1, IC3.1 (AVDDL_1)
unnamed: C75.1, IC3.11 (DVDDL_1), IC3.12 (AVDDL_2)
unnamed: C95.1, IC3.22 (AVDDL_3)
unnamed: C97.1, IC3.32 (AVDDL_4)
unnamed: C100.1, IC3.55 (AVDDL_5)
unnamed: C77.1, IC3.47 (DVDDL_3)
unnamed: IC3.54 (IBREF), R6.1
unnamed: C37.1, IC3.36 (RESETB), R8.2
unnamed: C38.1, IC3.48 (V10OUT)
unnamed: C178.1, IC5.1 (BS)
unnamed: IC5.4 (EN), R163.2, R164.1
unnamed: C179.1, IC5.3 (FB), R165.2, R166.1
unnamed: C178.2, IC5.6 (LX), L8.1
unnamed: J6.1, J6.2, R11.1, R25.1
unnamed: J6.9, R4.2
unnamed: J6.10, R7.1
unnamed: J6.11, R5.2
unnamed: J6.12, R9.1
unnamed: J6.13, Q1.3 (C), R3.1
unnamed: C35.2, J9.6
unnamed: C166.1, J10.1, L9.2
unnamed: D6.1, FL1.2, J14.3 (D+), R31.2
unnamed: D12.1, FL1.3, J14.2 (D-), R30.2
unnamed: J15.2, R147.2
unnamed: J15.4, R148.2
unnamed: J15.6, R149.2
unnamed: J15.8, R150.2
unnamed: J16.2, R151.2
unnamed: J16.4, R152.2
unnamed: J16.8, R153.2
unnamed: D4.1, D28.2, J7.2, J17.2
unnamed: J18.3, R51.1, R52.1, R53.1
unnamed: J19.3, R110.1, R111.1, R112.2
unnamed: J20.3, R114.1, R115.1, R116.1
unnamed: J26.3, R56.1, R57.1, R108.1
unnamed: D24.2, J32.1, Q2.3 (C), R160.2, R173.2
unnamed: C111.1, PS2.3 (EN), PS3.3 (EN), R124.2
unnamed: Q1.1 (B), R2.2
unnamed: Q2.1 (B), R159.2
unnamed: Q3.1 (B), R158.2
unnamed: D23.2, Q3.3 (C), R157.2
unnamed: Q4.1 (B), R170.2
unnamed: Q5.1 (B), R172.2
unnamed: R72.1, U17.P1_R_Led-
unnamed: R77.1, U17.P1_L_Led-
unnamed: R78.1, U17.P2_R_Led-
unnamed: R79.1, U17.P2_L_Led-
unnamed: R80.1, U17.P3_R_Led-
unnamed: R81.1, U17.P3_L_Led-
unnamed: R82.1, U17.P4_R_Led-
unnamed: R83.1, U17.P4_L_Led-
unnamed: R104.1, U18.P1_R_Led-
unnamed: R105.1, U18.P1_L_Led-
unnamed: R106.1, U18.P2_L_Led-
unnamed: R107.1, U18.P2_R_Led-
unnamed: R146.2, S1.1
unnamed: R154.2, U1.142
unnamed: C122.2, R125.1, U4.1 (XIN)
unnamed: C123.2, R128.2, U4.3 (XOUT), U8.3 (INA2)
unnamed: R15.2, U5.43 (ADC_AVDD)
unnamed: R17.2, U5.46 (USB_DM)
unnamed: R16.2, U5.47 (USB_DP)
unnamed: R20.1, U6.2 (~RE), U6.3 (DE)
unnamed: C54.1, U6B1.J6 (MIPI_VREFG)
unnamed: C44.2, C51.2, U6B1.D2 (REFB1)
unnamed: C45.2, C52.2, U6B1.F2 (REFB2)
unnamed: C42.2, C50.2, U6B1.H2 (REFB3)
unnamed: C40.2, C49.2, U6B1.K2 (REFB4)
unnamed: C47.2, C51.1, U6B1.C1 (REFT1)
unnamed: C48.2, C52.1, U6B1.E1 (REFT2)
unnamed: C46.2, C50.1, U6B1.G1 (REFT3)
unnamed: C43.2, C49.1, U6B1.J1 (REFT4)
unnamed: R118.1, U6B1.H7 (SA0)
unnamed: R117.1, U6B1.J5 (SA1)
unnamed: R120.2, R121.1, U6B1.J9 (SEL_18)
unnamed: R45.2, U6B1.L4 (SYS_CLK)
unnamed: R125.2, R128.1, U8.1 (INA1), U8.4 (OUT*Y2)
unnamed: C128.1, U8.5 (VCC)
unnamed: C30.1, U10.2 (FB)
unnamed: C174.1, D24.1, R161.2, R162.1, U10.4 (VC)
unnamed: D11.1, L3.1, U10.5 (VIN)
unnamed: R139.2, U14.3 (EN)
unnamed: C171.1, D23.1, R155.2, R156.1, U15.2 (FB)
unnamed: D10.1, L2.1, U15.3 (SW)
unnamed: C170.1, U15.4 (VC)
unnamed: D2.1, U17.4_1, U17.5_1
unnamed: D5.1, U17.4_2, U17.5_2
unnamed: D7.1, U17.4_3, U17.5_3
unnamed: D8.1, U17.4_4, U17.5_4
unnamed: D1.1, U18.4_1, U18.5_1
unnamed: D9.1, U18.4_2, U18.5_2
PCIE_CLK_NREQ: J3.7, J8.52, U1.92
PCIE_NRST: J3.8, J8.50, U1.90
RS485_A: J5.3, R40.1, U6.6 (A)
RS485_B: J5.2, R41.1, U6.7 (B)
RX: R19.1, U5.7 (GPIO5), U6.1 (RO)
RX0_N: U13.12, U17.2_1
RX0_P: U13.11, U17.1_1
RX1_N: U13.19, U17.2_2
RX1_P: U13.20, U17.1_2
RX2_N: U12.12, U17.2_3
RX2_P: U12.11, U17.1_3
RX3_N: U12.19, U17.2_4
RX3_P: U12.20, U17.1_4
RX4_N: U18.2_1, U19.12
RX4_P: U18.1_1, U19.11
RX5_N: U18.2_2, U19.19
RX5_P: U18.1_2, U19.20
TX: R18.1, U5.6 (GPIO4), U6.4 (DI)
TX0_N: U13.14, U17.6_1
TX0_P: U13.15, U17.3_1
TX1_N: U13.17, U17.6_2
TX1_P: U13.16, U17.3_2
TX2_N: U12.14, U17.6_3
TX2_P: U12.15, U17.3_3
TX3_N: U12.17, U17.6_4
TX3_P: U12.16, U17.3_4
TX4_N: U18.6_1, U19.14
TX4_P: U18.3_1, U19.15
TX5_N: U18.6_2, U19.17
TX5_P: U18.3_2, U19.16
VCC_3V3_S0: C147.1, C148.1, C154.1, C156.1, IC2.6 (AVDD33), IC2.18 (DVDD33), IC2.28 (AVDD33_1), IC2.34 (AVDD33_2), IC2.47 (AVDD33_3), L6.2, R132.1, R134.2, R136.2, R137.1, R139.1, R140.2, R141.2, TP12.1, U14.1 (IN)
VDD12: C112.1, C116.1, C120.1, C124.1, C126.1, L4.2, U6B1.D6 (DVDD12.2), U6B1.D8 (DVDD12.4), U6B1.F8 (DVDD12.5), U6B1.G6 (DVDD12.3), U6B1.H5 (DVDD12.1)
VIN: C28.1, C29.2, C30.2, C83.1, C169.2, C170.2, D28.1, D29.1, J4.5, J5.4, J5.5, J13.4, J13.8, K1.3 (NO), K3.3 (NO), R49.1, TP4.1, TP6.1, TP7.1, U2.2 (IN), U3.2 (IN), U10.3 (SW), U15.5 (VIN)
VRAW: D29.2, J11.1, TP5.1
XI: C39.1, IC3.52 (XI), Y4.1
XO: C61.1, IC3.51 (XO), Y4.3

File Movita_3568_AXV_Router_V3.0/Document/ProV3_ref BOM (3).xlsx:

Id | Designator | Footprint | Quantity | Designation | 1010pcs
1 | R15 | R_0603_1608Metric | 1 | 1R
2 | C17,C16,C24,C20,C26,C22,C27,C21,C23,C25,C8,C11,C9,C13 | C_0402_1005Metric | 14 | 100nF
3 | R130 | R_0402_1005Metric | 1 | 10K %1
4 | R169,R171,R158,R2,R3,R36,R18,R40,R19,R35,R20,R43,R119,R44,R164,R41,R124,R159,R1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 | R_0603_1608Metric | 53 | 10K
5 | R109,R5,R4,R113,R123,R25,R9,R126,R7,R54,R46,R127,R11 | R_0603_1608Metric | 13 | 0R
6 | C138,C137,C134,C141,C142,C136,C132,C130,C133,C135,C112,C129,C113,C131 | C_0402_1005Metric | 14 | 10uF
7 | U19,U13,U12 | RJ45_Transformer_2_Port | 3 | TF-218DG
8 | C4,C12,C6,C154,C149 | C_0603_1608Metric | 5 | 4.7uF
9 | R133,R139,R131,R134 | R_0402_1005Metric | 4 | 0R
10 | C92,C93 | S102K33Y5PP63K5R | 2 | 1000PF 2KV
11 | C171,C174 | C_0603_1608Metric | 2 | 0.33uF 16V
12 | D23,D24 | LL4148 | 2 | LL4148
13 | IC2 | QFN-48-1EP_7x7mm_P0.5mm_EP5.6x5.6mm | 1 | MS1836S_QFN48-7x7
14 | C84,C170,C30,C172,C169,C29 | C_0603_1608Metric | 6 | 1uF/50V
15 | D28,D29 | S6MC | 2 | S6MC
16 | FL4,FL3 | BLM18AG102BH1D | 2 | BLM18PG121SN1D
17 | D15,D14,D17,D16 | D_SOD-123 | 4 | B5819W
18 | R116,R53,R125,R45,R112,R108, R146 | R_0603_1608Metric | 6 | 100R
19 | R30,R31 | R_0402_1005Metric | 2 | 2.2R
20 | U1 | CM3568 | 1 | ~ | Fatih supply this part
21 | R57,R115,R52,R110,R111,R114,R51,R102,R75,R73,R103,R76,R74,R56 | R_0603_1608Metric | 14 | 75R
22 | R150,R148,R152,R149,R153,R147,R151 | R_0603_1608Metric | 7 | 220R
23 | C48,C47,C43,C44,C46,C116,C109,C56,C49,C182,C183,C51,C103,C58,C42,C104,C126,C60,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 | C_0603_1608Metric | 61 | 0.1uF
24 | C18,C128,C19,C53,C139,C140 | C_0603_1608Metric | 6 | 1uF
25 | PS3 | SOT95P280X145-5N | 1 | TLV75712PDBVR
27 | J16,J15 | LED_4_Block | 2 | Conn_01x08_Socket
28 | D11,D10 | DIOM5336X244N | 2 | SS54B
29 | C39,C61 | C_0603_1608Metric | 2 | 33pF
30 | R21,R48,R13,R12,R10,R24,R89,R90,R83,R93,R84,R23,R92,R85,R91,R81,R106,R77,R42,R3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 | R_0603_1608Metric | 30 | 1K
31 | J13 | PinSocket_2x04_P2.00mm_Vertical_SMD | 1 | FEMALE SMD Pin Header
33 | D19,D20,D21,D18 | D_SMA | 4 | SMAJ30CA
34 | TP5,TP15,TP13,TP4,TP1,TP14,TP7,TP3,TP2,TP9,TP11,TP12,TP8,TP10,TP6 | Pin_D1.0mm_L10.0mm | 15 | TestPoint
35 | C145,C146,C179 | C_0603_1608Metric | 3 | 22pF
36 | Q4,Q3,Q5,Q2 | MMBT2222ALT1G | 4 | MMBT2222ALT1G
37 | R22,R173,R167,R29,R26,R154,R50 | R_0603_1608Metric | 7 | DNP
38 | C180,C181,C62,C69 | C_0603_1608Metric | 4 | 22uF
39 | C38,C36,C99,C77,C100,C98,C74,C178,C111,C75,C97,C96,C95 | C_0603_1608Metric | 13 | 100nF
40 | R17,R16 | R_0603_1608Metric | 2 | 27R
41 | J30,J29,J35 | MountingHole_3.2mm_M3_ISO7380_Pad | 3 | Screw_Terminal_01x01
42 | Q1 | 2N3904S-RTKPS | 1 | 2N3904S-RTK/PS
43 | R143 | R_0402_1005Metric | 1 | 75R
44 | C164 | C_0603_1608Metric | 1 | DNP
45 | C10,C7,C37,C151,C155 | C_0603_1608Metric | 5 | 10uF
46 | C76,C66,C63,C68,C71,C72,C73,C67,C65,C64,C81,C78,C91,C86,C70,C89,C87,C88,C90,C85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 | C_0402_1005Metric | 22 | 0.1uF
47 | U18 | 2_Block_RJ45 | 1 | ~
48 | U3,U2 | SOT-23 | 2 | TLV76033DBZT
49 | D30,D6,D13,D12 | ESD5341N | 4 | ESD5341N
50 | J2,J26,J20,J18,J19 | AV_CON | 5 | Phono _RCA_ Jack Mono Connector Solder
51 | R162 | R_0603_1608Metric | 1 | 1.6K
52 | D22 | ESD5451N | 1 | ESD5451N
54 | R135 | R_0603_1608Metric | 1 | 330R %1
55 | L6 | L_0603_1608Metric | 1 | UPZ1608E101-3R0TF
56 | U5 | RP2040-QFN-56 | 1 | RP2040
57 | J27 | PinHeader_1x07_P1.00mm_Vertical | 1 | DNP
58 | D26,D27 | D_0603_1608Metric | 2 | MRA4007T3G
59 | D4,D5,D7,D2,D1,D8,D9 | 2SS100LW | 7 | 2SS100L-W
60 | R14 | R_0603_1608Metric | 1 | 200R
62 | K1,K3 | HF46F5HS1 | 2 | HF46F_5-HS1
63 | IC3 | RTL8309N | 1 | RTL8309N
64 | J22,J21 | PinSocket_2x04_P2.54mm_Vertical_SMD | 2 | FEMALE SMD Pin Header
65 | J32 | PinHeader_1x02_P2.54mm_Vertical | 1 | DNP
66 | C166,C35,C94 | C_0603_1608Metric | 3 | 10pF
67 | R34,R33,R32,R120,R118,R117,R27,R28 | R_0603_1608Metric | 5 | 4.7K
68 | U4 | Oscillator_SMD_EuroQuartz_XO32-4Pin_3.2x2.5mm | 1 | 3N27000G33YC
71 | C83,C28 | C_Elec_10x10.2 | 2 | 220uF/50V
72 | C177,C176,C175 | C_0603_1608Metric | 3 | 10uF /16V
73 | J10 | SMA_Connector_inner_pin_right_angle | 1 | SMA Connetor_inner_hole
74 | C32,C82 | C_Elec_8x10.2 | 2 | 330uF/25V
75 | R168 | R_0603_1608Metric | 1 | 2K
76 | C153 | C_0603_1608Metric | 1 | 10nF
77 | R8,R6 | R_0603_1608Metric | 2 | 2.49K 1%
78 | U6 | SOIC127P600X175-8N | 1 | MAX485E
80 | R157,R160 | R_0603_1608Metric | 2 | 470R
81 | U17 | 4_Block_RJ45 | 1 | RJ45-4-Block
82 | Y2 | Crystal_SMD_3225-4Pin_3.2x2.5mm | 1 | X322527MSB4SI
83 | S1 | TS-1101-C-W | 1 | TS-1101-C-W
84 | J4 | PinSocket_1x05_P2.00mm_Vertical | 1 | DNP
85 | L7 | L_0603_1608Metric | 1 | MLI1608F-1R2KT
86 | R166 | R_0603_1608Metric | 1 | 51K_1%
87 | J6 | PinHeader_2x20_P1.27mm_Vertical | 1 | MALE SMD Pin Header
88 | R138,R129 | R_0402_1005Metric | 2 | DNP
89 | R144 | R_0603_1608Metric | 1 | 100K
90 | C184 | CP_Elec_6.3x7.7 | 1 | 220uF/16V
92 | C122,C123 | C_0603_1608Metric | 2 | 8pF
93 | U15,U10 | TO-263-5_TabPin3 | 2 | XL4015
95 | J17 | JST_PH_B2B-PH-K_1x02_P2.00mm_Vertical | 1 | Conn_01x02_Socket
96 | R163 | R_0603_1608Metric | 1 | DNP
97 | J12 | KF2EDGH-3.81_8P | 1 | Conn_01x08_Socket
99 | J1 | PinSocket_2x07_P2.54mm_Vertical_SMD | 1 | FEMALE SMD Pin Header
100 | J33 | PinSocket_2x02_P2.54mm_Vertical_SMD | 1 | FEMALE SMD Pin Header
101 | U8 | SOP95P275X110-6N | 1 | NL27WZU04DTT1G
102 | C15,C14 | C_0603_1608Metric | 2 | 27pF
103 | FL1 | DLW31SH222SQ2L | 1 | DLW31SN900SQ2L
104 | J28,J23 | Screw_terminal_shinbo | 2 | M3x*0.5 L=10
105 | R161 | R_0603_1608Metric | 1 | 15K
107 | U14 | SOT-23-5 | 1 | RT9013-12GB
108 | L3,L2 | L_Bourns_SRR1208_12.7x12.7mm | 2 | 47uH 5A
109 | R165 | R_0603_1608Metric | 1 | 232K_1%
110 | R128 | R_0603_1608Metric | 1 | 560K
111 | U7 | SOIC-8_5.23x5.23mm_P1.27mm | 1 | W25Q128JVS
112 | D25 | LED_0603_1608Metric | 1 | LED
113 | J11 | KF2EDGR-Y-5.08-3P-Right Angle | 1 | Conn_01x03_Socket
114 | J3 | PinSocket_2x04_P2.54mm_Vertical_SMD | 1 | DNP
115 | L9 | L_0603_1608Metric | 1 | 2.7nH
116 | R145 | R_0603_1608Metric | 1 | 1K %5
117 | Y4 | Crystal_SMD_3225-4Pin_3.2x2.5mm | 1 | 25MHz
118 | J14 | KH-MICRO5P-JN | 1 | KH-MICRO5P-JN
119 | L8 | Inductor_0402_4.7uH | 1 | HA42-4R7MT
120 | PS2 | SOT94P279X130-5N | 1 | RT9013-33GB
121 | J34 | PinSocket_1x03_P2.54mm_Vertical_SMD_Pin1Left | 1 | FEMALE SMD Pin Header
122 | R142 | R_0603_1608Metric | 1 | 22R
124 | L4,L5 | L_0603_1608Metric | 2 | FB/100R
125 | U6B1 | N4 | 1 | Nextchip N4
126 | J5 | RJ45_Amphenol_54602-x08_Horizontal | 1 | RJ45
127 | C114,C115 | C_0402_1005Metric | 2 | 4.7uF
128 | J25 | PinHeader_2x02_P2.54mm_Vertical_SMD | 1 | DNP
129 | IC5 | SOT95P285X100-6N | 1 | SY8113B
130 | R156 | R_0603_1608Metric | 1 | 3.3K 1%
131 | J7 | KF2EDGH-3.81-2P | 1 | Conn_01x02_Socket
132 | IC1 | SN74LVC125APWR | 1 | SN74LVC125APWR
133 | J9 | RTL8188EU | 1 | Conn_01x06_Pin
134 | J31 | PinSocket_2x01_P2.54mm_Vertical_SMD | 1 | DNP
135 | C5 | CAPPRD508W154D1200H850 | 1 | FYD0H473ZF
136 | R141,R140 | R_0603_1608Metric | 2 | 2.2K
139 | Y1 | Crystal_SMD_3225-4Pin_3.2x2.5mm | 1 | 12000Mhz
140 | J24 | CP-USB-3015 | 1 | USB 3.0 AF
141 | FB1 | BEADC3216X130N | 1 | HI1206N101R-10
142 | J8 | TE_1-2199119-5 | 1 | APCI0079-P002A J8900 M.2 M Key
143 | R1 | R_0603_1608Metric | 1 | 150R
144 | U16 | SATA_Connector_5622-1200-ML | 1 | 5622-1200-ML
145 | R121 | R_0402_1005Metric | 1 | DNP
146 | U11 | module_mpu6050 | 1 | DNP
147 | D3 | DIOM4325X250N | 1 | SS14
